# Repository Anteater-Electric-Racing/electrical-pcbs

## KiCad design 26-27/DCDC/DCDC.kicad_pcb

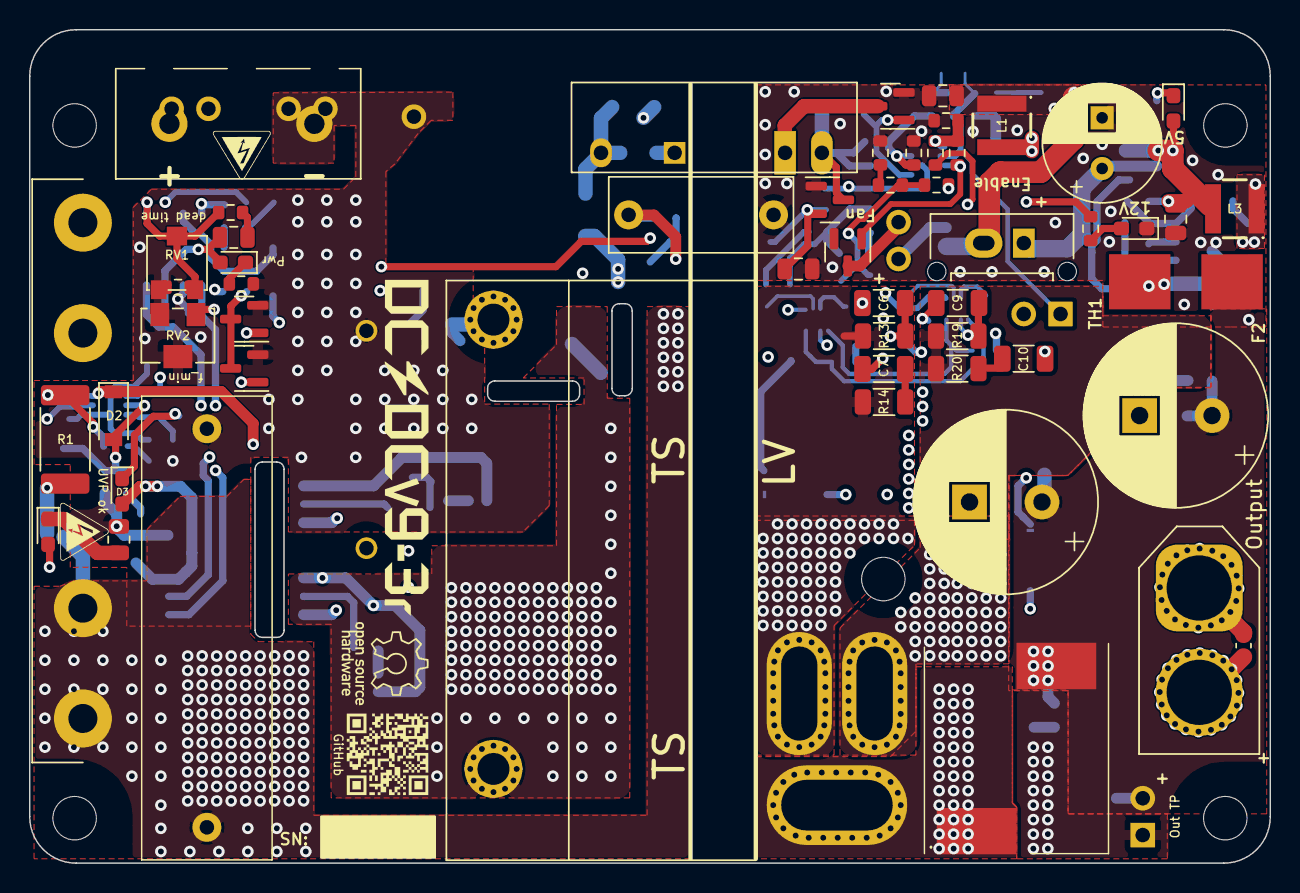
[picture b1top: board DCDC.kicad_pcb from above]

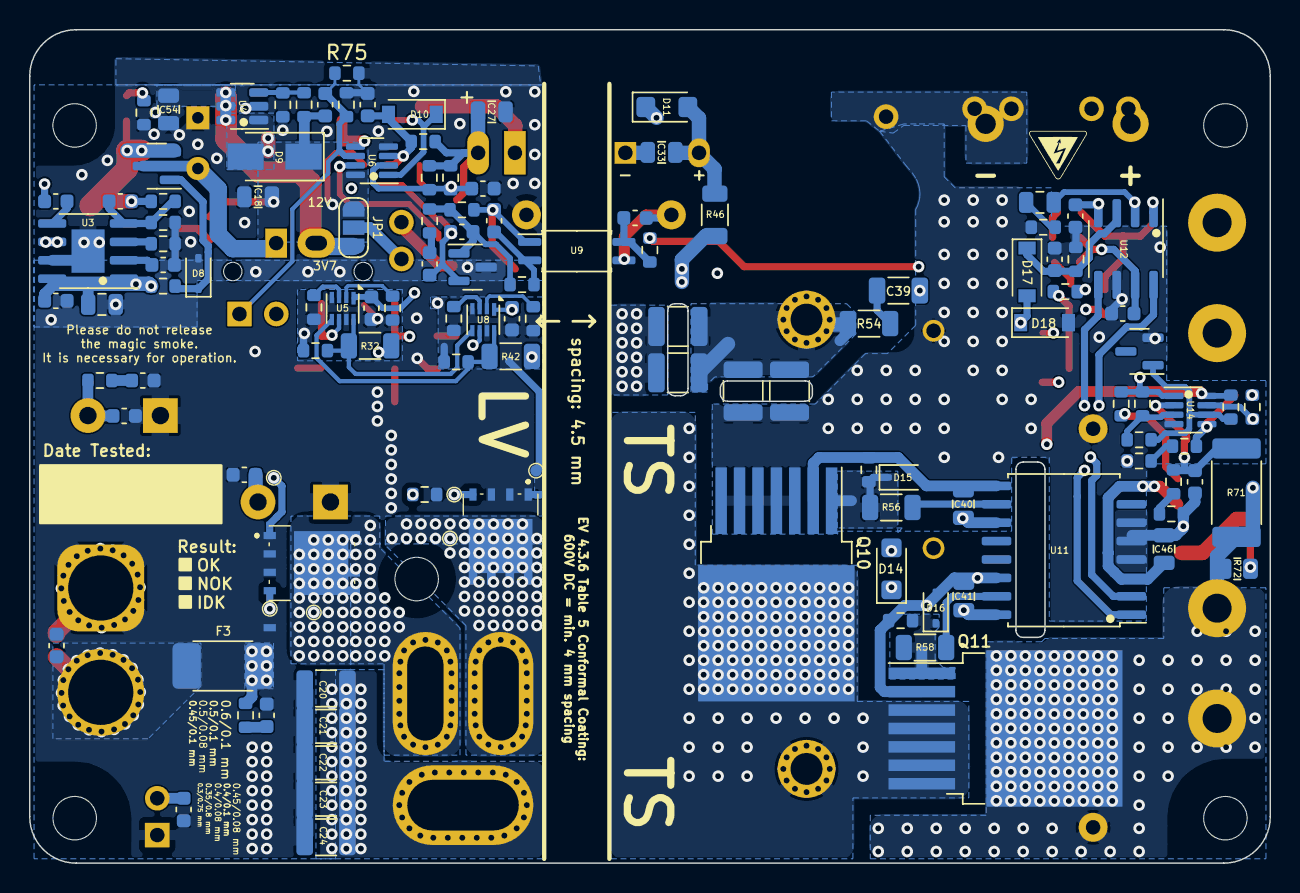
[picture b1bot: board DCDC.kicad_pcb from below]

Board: 4 copper layers, 85.6 x 57.5 mm, 189 parts (128 on the bottom side), 91 nets.

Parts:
C1: 2uF; MKP1848520704K2
C2, C15, C40, C41: 2.2uF; C_0805_2012Metric
C3: 22nF; R76UI22205050J
C4: 3.3nF; C_Disc_D12.5mm_W5.0mm_P10.00mm
C5, C33, C46: 10uF; C_0805_2012Metric
C6, C9: 1 nF; C_1206_3216Metric
C7, C10, C39: 470pF; C_1206_3216Metric
C8, C12, C18, C27, C42, C54: 22uF; C_0805_2012Metric
C11, C13: 2200uF; CP_Radial_D12.5mm_P5.00mm_symbol_inside
C14, C28: 100nF; C_0603_1608Metric
C16, C49, C50, C51, C52, C53, C55, C56, C57: 1nF; C_0603_1608Metric
C17, C19, C25, C31, C45: 1uF; C_0603_1608Metric
C20, C21, C22, C23, C24: 10uF; C_1210_3225Metric
C26, C44, C47: 22nF; C_0603_1608Metric
C29: 47pF; C_0603_1608Metric
C30, C32, C48: 10nF; C_0603_1608Metric
C34, C35, C36, C37: 5.6nF; C_1210_3225Metric
C43: 470nF; C_0603_1608Metric
C_start1: 3.8V 25F Supercap; CP_Radial_D8.0mm_P3.50mm
D1: HV_Orange; LED_0603_1608Metric_Pad1.05x0.95mm_HandSolder
D2, D10, D17, D18: 1N4448; D_SOD-123
D3, D4, D6, D7: Green; LED_0603_1608Metric_Pad1.05x0.95mm_HandSolder
D8, D15, D16: CDSOD323-T12; D_SOD-323
D9: SS1H10; D_SMA
D11, D14: VS-E7FX0212-M3/I; D_SMF
F1: 1.6A; Fuseholder0,25Zoll_32mm_littlefuse_102_122
F2: 500mA; NANO-0154-OMNI-BLOK-Fuse-Holder
F3: 20A; Bel_SMCF_Fuse_2410_6125Metric
HV_Logo_1, HV_Logo_1#2, HV_Logo_1#3: HV_Logo_1; HV_Logo_small
J1: Screw_Terminal_01x03; TerminalBlock_TE-282817-2_1x03_P5.00mm_90 Degrees updated v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
J2, J4, J6, J7, J8: Conn_01x02_Male; PinHeader_1x02_P2.54mm_Vertical
J3: Conn_01x02; Molex_Micro-Fit_3.0_43650-0215_1x02_P3.00mm_Vertical_combin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
J5: XT60 Male; AMASS_XT60-F_1x02_P7.20mm_Vertical
JP1: Fan Voltage Select; SolderJumper-3_P1.3mm_Open_RoundedPad1.0x1.5mm_NumberLabels
L1: 4.7uH; ASPI-4030S
L2: 1uH; 7443091100_v9.2
L3: 10uH; ASPI-4030S
NT1, NT2: NetTie_2; dummy_net_line_0.5mm
Q1, Q2, Q5, Q6, Q7: PMV20ENR; SOT-23
Q8, Q9: BSC027N06LS5ATMA1
Q10, Q11: IMBG65R050M2HXTMA1; TO-263-7_TabPin8
QR_Coode_1: QR_Coode; GitHub_QR_Code
R1, R71: 100M; R_2512_6332Metric_Pad1.40x3.35mm_HandSolder
R2, R72: 330k; R_0805_2012Metric
R3: 3.0k; R_0603_1608Metric
R4, R39, R41, R59, R61: 1k; R_0603_1608Metric
R5, R11, R15, R16, R21, R23, R30, R33, R40, R43, R55, R57, R63: 10k; R_0603_1608Metric
R10, R22, R29, R38: 2.2k; R_0603_1608Metric
R12: 910; R_0603_1608Metric
R13, R19: 100; R_1206_3216Metric
R14, R20: 47; R_1206_3216Metric
R17, R24: 27k; R_0603_1608Metric
R18, R27: 470k; R_0603_1608Metric
R25: 240k; R_0603_1608Metric
R26, R67, R70, R75: 100k; R_0603_1608Metric
R28, R34, R66: 33k; R_0603_1608Metric
R31, R36: 4.7k; R_0603_1608Metric
R32, R42: 4.7; R_1206_3216Metric
R35: 330k; R_0603_1608Metric
R37: 47k; R_0603_1608Metric
R44: 510; R_0603_1608Metric
R46: 20; R_1206_3216Metric
R54: 10M; R_1206_3216Metric
R56, R58: 10; R_1206_3216Metric
R60: 82k; R_0603_1608Metric
R62, R69: 100M; R_0603_1608Metric
R64: 820k; R_0603_1608Metric
R65: 510k; R_0603_1608Metric
R68: 1.6M; R_0603_1608Metric
R73, R74: 10; R_0603_1608Metric
RV1: 20k; Potentiometer_Bourns_PVG3G
RV2: 10k; Potentiometer_Bourns_3214W_Vertical
T1: DIY Transformer ETD 39; Transformer_ETD39_uprightV3.6 (PSS 24V)
TH2: 1k PTC; R_0603_1608Metric
TP1, TP2, TP3, TP4, TP5, TP6: TestPoint; TestPoint_Pad_D0.8mm_DC-DC
TP8: GaN GND2; TestPoint_Pad_D0.8mm_DC-DC
U1: TBA 1-1212HI; Converter_DCDC_TRACO_TBA 1-1212HI-3kV-iso
U2: RT9058-90GVL; SOT-23
U3: MP4541_SOP8-EP; SOIC-8-1EP_3.9x4.9mm_P1.27mm_EP2.29x3mm XL7005
U4: TLV61048DBVR; SOT-23-6
U5, U8: NCP4305DMTTWG; WDFN-8_2x2mm_P0.5mm
U6, U14: LM2904BIDDFR; SOT-23-8_DC-DC_v9
U7: TL431; SOT-23
U9: ACPL-217-50AE; SOIC-4_4.55x2.6mm_P1.27mm
U11: UCC21520DWR; SOIC-16W_7.5x10.3mm_P1.27mm
U12: UCC25600; SOIC-8_3.9x4.9mm_P1.27mm
U13: ZXRE330ASA-7; SOT-23

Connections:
24V_TP: C11.1, C13.1, C50.2, C51.2, C52.2, F2.1, F3.1, J4.1, L2.2, R17.1, R73.1, R74.1
+3V7: C8.1, C54.1, J3.2, JP1.3 (B), L1.1, U4.4 (~SHDN), U4.5 (IN), U4.6 (nc)
+9V: C5.1, C30.2, R39.1, U2.2 (VO), U9.1
+12V_HS: C41.2, D14.1 (K), U11.16 (VDDA)
+12V_IN: C2.2, C40.2, C45.2, C46.1, D2.1 (K), D3.2 (A), D4.2 (A), D11.1 (K), R70.1, U11.3 (VCCI), U11.8 (VCCI), U11.11 (VDDB), U12.7 (VCC), U14.8 (V+)
+12V_sw: C18.1, C19.2, C25.1, C27.1, C31.1, D9.1 (K), J8.1, JP1.1 (A), R16.1, R21.2, R27.1, R34.1, R35.2, R36.2, U1.1 (+VIN), U2.3 (VI), U5.1 (VCC), U6.8 (V+), U8.1 (VCC)
+24V: C15.2, C53.2, F2.2, R26.2, U3.1 (EN), U3.8 (VIN)
+HV: C1.2, C34.1, C35.1, F1.2, Q11.8 (D), R1.1, R71.1, R72.1
+HV_in: F1.1, J1.2, J7.1, J7.2
-HV_in: C1.1, C3.2, C4.1, C32.2, C33.2, C36.2, C37.2, C43.2, C44.1, C45.1, C46.2, C47.2, D18.2 (A), J1.1, J6.1, J6.2, Q1.2 (S), Q2.2 (S), Q10.3 (S), Q10.4 (S), Q10.5 (S), Q10.6 (S), Q10.7 (S), R2.2, R3.2, R5.1, R59.2, R60.1, R65.2, R68.2, RV1.3, RV2.2, RV2.3, U1.5 (-VOUT), U9.3, U11.4 (GND), U11.5 (DIS), U11.6 (DT), U12.6 (GND), U13.2, U14.4 (V-)
/HB_out: Q10.8 (D), Q11.3 (S), Q11.4 (S), Q11.5 (S), Q11.6 (S), Q11.7 (S), T1.1 (AA)
/HS: U11.1 (INA), U12.8 (GD1)
/LS: U11.2 (INB), U12.5 (GD2)
/OC: C44.2, D17.1 (K), R60.2, U12.3 (OC)
/OTP_FAN: Q5.1 (G), R18.1, U6.7
/OTP_OFF: D10.1 (K), Q6.1 (G), U6.1
/OVP: Q2.1 (G), R69.1, U14.7
/Opc+: C32.1, R44.2, U9.4
/Synchronous Rectification/3: Q9.5 (D_1), Q9.6 (D_2), Q9.7 (D_3), Q9.8 (D_4), Q9.9 (D_5), R13.2, R14.1, T1.3 (SB), TP5.1
/Synchronous Rectification/5: Q8.5 (D_1), Q8.6 (D_2), Q8.7 (D_3), Q8.8 (D_4), Q8.9 (D_5), R19.2, R20.1, T1.5 (SA), TP3.1
/UVP: Q1.1 (G), R62.1, R63.1, U14.1
GND: C4.2, C5.2, C7.1, C8.2, C10.1, C11.2, C12.1, C13.2, C15.1, C17.1, C18.2, C20.2, C21.2, C22.2, C23.2, C24.2, C27.2, C28.1, C48.1, C49.1, C50.1, C51.1, C52.1, C53.1, C54.2, C55.1, C56.1, C57.1, C_start1.2 (-), D6.1 (K), D8.2 (A2), J4.2, J5.2, NT1.2, NT2.2, Q5.2 (S), Q6.2 (S), Q8.1 (S_1), Q8.2 (S_2), Q8.3 (S_3), Q9.1 (S_1), Q9.2 (S_2), Q9.3 (S_3), R10.2, R11.2, R15.1, R22.1, R23.2, R25.1, R28.2, R31.1, R75.2, TH2.2, TP8.1, U2.1 (GND), U3.7 (GND), U4.2 (GND), U6.4 (V-), U7.3 (A)
unnamed: C2.1, R4.2
unnamed: C7.2, R14.2
unnamed: C10.2, R20.2
unnamed: C26.2, R37.1
unnamed: C30.1, R41.1, U9.2
unnamed: C39.2, R54.1
unnamed: C42.2, R59.1
unnamed: C56.2, R73.2
unnamed: C57.2, R74.2
unnamed: C_start1.1 (+), J3.1, Q7.3 (D)
unnamed: D1.2 (A), R72.2
unnamed: D1.1 (K), R2.1
unnamed: C47.1, D2.2 (A), R67.2, R71.2, U14.2 (-)
unnamed: D3.1 (K), R63.2
unnamed: D4.1 (K), R5.2
unnamed: D6.2 (A), R21.1
unnamed: C12.2, C16.2, D7.2 (A), L3.2, Q7.2 (S), R24.1
unnamed: D7.1 (K), R22.2
unnamed: D8.1 (A1), Q7.1 (G), R26.1
unnamed: D9.2 (A), L1.2, U4.1 (SW)
unnamed: C48.2, D10.2 (A), R11.1, R34.2, U6.3 (+)
unnamed: C33.1, D11.2 (A), R46.2, U1.7 (+VOUT)
unnamed: D14.2 (A), R46.1
unnamed: D15.1 (A1), Q10.1 (G), R55.1, R56.1
unnamed: C40.1, D15.2 (A2), Q10.2 (DS), R55.2, U11.9 (VSSB)
unnamed: D16.1 (A1), Q11.1 (G), R57.1, R58.1
unnamed: C41.1, D16.2 (A2), Q11.2 (DS), R57.2, U11.14 (VSSA)
unnamed: C39.1, D17.2 (A), D18.1 (K)
unnamed: J2.1, JP1.2 (C)
unnamed: J2.2, Q5.3 (D)
unnamed: C49.2, C55.2, F3.2, J5.1
unnamed: C19.1, J8.2, R31.2, R75.1, U6.6 (-)
unnamed: Q1.3 (D), Q2.3 (D), R61.1
unnamed: Q8.4 (G), R32.1, TP2.1
unnamed: Q9.4 (G), R42.1, TP4.1
unnamed: R10.1, R12.2
unnamed: R65.1, R66.2
unnamed: R67.1, R68.1
unnamed: C34.2, C35.2, C36.1, C37.1, R54.2, T1.2 (AB)
unnamed: C20.1, C21.1, C22.1, C23.1, C24.1, L2.1, T1.4 (SC)
unnamed: C14.2, U3.5 (BST)
unnamed: C16.1, R23.1, R24.2, U3.4 (FB)
unnamed: R25.2, U3.3 (FREQU)
unnamed: C14.1, L3.1, U3.6 (SW)
unnamed: C17.2, U3.2 (VCC)
unnamed: R27.2, R28.1, U4.3 (FB)
unnamed: C9.2, R19.1, U5.6 (CS)
unnamed: R30.2, R32.2, U5.8 (DRV), U8.5 (TRIG/DIS)
unnamed: C9.1, C25.2, NT1.1, R29.1, R30.1, R33.1, TP1.1, U5.4 (LLD), U5.7 (GND)
unnamed: R33.2, U5.2 (MIN_TOFF)
unnamed: R29.2, U5.3 (MIN_TON)
unnamed: R40.2, R42.2, U5.5 (TRIG/DIS), U8.8 (DRV)
unnamed: C28.2, R35.1, R36.1, TH2.1, U6.2 (-)
unnamed: R15.2, R16.2, R18.2, U6.5 (+)
unnamed: C29.2, R37.2, R39.2, R41.2, U7.1 (K)
unnamed: C26.1, C29.1, R12.1, R17.2, U7.2 (REF)
unnamed: C6.2, R13.1, U8.6 (CS)
unnamed: C6.1, C31.2, NT2.1, R38.1, R40.1, R43.1, TP6.1, U8.4 (LLD), U8.7 (GND)
unnamed: R43.2, U8.2 (MIN_TOFF)
unnamed: R38.2, U8.3 (MIN_TON)
unnamed: R58.2, U11.15 (OUTA)
unnamed: R56.2, U11.10 (OUTB)
unnamed: R3.1, R4.1, RV1.1, RV1.2, U12.1 (DT)
unnamed: C42.1, R44.1, RV2.1, U12.2 (RT)
unnamed: C43.1, R61.2, U12.4 (SS)
unnamed: R62.2, R64.1, U14.3 (+)
unnamed: R1.2, R66.1, R69.2, U14.5 (+)
unnamed: R64.2, R70.2, U13.1, U14.6 (-)
OTP_FET: Q6.3 (D), U1.2 (-VIN)

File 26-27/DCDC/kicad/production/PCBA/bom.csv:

Designator,Footprint,Quantity,Value,LCSC Part #
C1,MKP1848520704K2,1,2uF,
"C11, C13",CP_Radial_D12.5mm_P5.00mm_symbol_inside,2,2200uF,
"C12, C18, C27, C42, C54, C8",0805,6,22uF,
"C14, C28",0603,2,100nF,
"C15, C40, C41",0805,3,2.2uF,
"C16, C49, C50, C51, C52, C53, C56, C57",0603,8,1nF,
"C17, C19, C25, C31, C45",0603,5,1uF,
"C20, C21, C22, C23, C24",1210,5,10uF,
"C26, C44, C47",0603,3,22nF,
C29,0603,1,47pF,
"C30, C32, C48",0603,3,10nF,
"C33, C46, C5",0805,3,10uF,
"C34, C35, C36, C37",1210,4,5.6nF,
C39,1206,1,470pF,
C4,C_Disc_D12.5mm_W5.0mm_P10.00mm,1,3.3nF,
C43,0603,1,470nF,
"C6, C9",1206,2,1 nF,
C_START1,CP_Radial_D8.0mm_P3.50mm,1,3.8V 25F Supercap,
D1,0603,1,HV_Orange,
"D10, D17, D18, D2",D_SOD-123,4,1N4448,
"D11, D12, D14",D_SMF,3,VS-E7FX0212-M3/I,
"D13, D9",D_SMA,2,SS1H10,
"D15, D16, D8",D_SOD-323,3,CDSOD323-T12,
"D3, D4, D5, D6, D7",0603,5,Green,
F1,"Fuseholder0,25Zoll_32mm_littlefuse_102_122",1,1.6A,
F2,NANO-0154-OMNI-BLOK-Fuse-Holder,1,500mA,
F3,Bel_SMCF_Fuse_2410_6125Metric,1,20A,
J1,43650-03YY_151617,1,43650-0315,
"J2, J4, J8",PinHeader_1x02_P2.54mm_Vertical,3,Conn_01x02_Male,
J3,Molex_Micro-Fit_3.0_43650-0215_1x02_P3.00mm_Vertical_combined2.54pinheader,1,Conn_01x02,
J5,AMASS_XT60-F_1x02_P7.20mm_Vertical,1,XT60 Male,
JP1,SolderJumper-3_P1.3mm_Open_RoundedPad1.0x1.5mm_NumberLabels,1,Fan Voltage Select,
L1,ASPI-4030S,1,4.7uH,
L2,7443091100_v9.2,1,1uH,
L3,ASPI-4030S,1,10uH,
"Q1, Q2, Q5, Q6, Q7",SOT-23,5,PMV20ENR,
"Q10, Q11",TO-263-7_TabPin8,2,IMBG65R050M2HXTMA1,
Q3,TO-220-3_Vertical_HV1.2mm,1,SIHP24N80AE-GE3,
Q4,TO-220-3_Vertical_HV1.2mm,1,IXYP8N90C3,
"Q8, Q9",BSC027N06LS5ATMA1,2,BSC027N06LS5ATMA1,
"R1, R71",2512,2,100M,
"R10, R22, R29, R38, R48, R49, R8",0603,7,2.2k,
"R11, R15, R16, R21, R23, R30, R33, R40, R43, R5, R51, R52, R55, R57, R63, R7, R9",0603,17,10k,
R12,0603,1,910,
"R13, R19",1206,2,100,
"R17, R24",0603,2,27k,
"R18, R27, R50",0603,3,470k,
"R2, R72",0805,2,330k,
R25,0603,1,240k,
"R26, R45, R47, R53, R67, R70, R75",0603,7,100k,
"R28, R34, R66",0603,3,33k,
"R31, R36",0603,2,4.7k,
"R32, R42",1206,2,4.7,
R35,0603,1,330k,
R37,0603,1,47k,
"R39, R41, R59, R61",0603,4,1k,
R44,0603,1,510,
R46,1206,1,20,
R54,1206,1,10M,
"R56, R58",1206,2,10,
R6,1206,1,47,
R60,0603,1,82k,
"R62, R69",0603,2,100M,
R64,0603,1,820k,
R65,0603,1,510k,
R68,0603,1,1.6M,
"R73, R74",0603,2,10,
RV1,Potentiometer_Bourns_PVG3G,1,20k,
RV2,Potentiometer_Bourns_3214W_Vertical,1,10k,
T1,Transformer_ETD39_uprightV3.6 (PSS 24V),1,DIY Transformer ETD 39,
TH2,0603,1,1k PTC,
U1,Converter_DCDC_TRACO_TBA 1-1212HI-3kV-iso,1,RP-1212S,
"U10, U14, U6",SOT-23-8_DC-DC_v9,3,LM2904BIDDFR,
U11,SOIC-16W_7.5x10.3mm_P1.27mm,1,UCC21520DW,
U12,SOIC-8_3.9x4.9mm_P1.27mm,1,UCC25600,
U13,SOT-23,1,ZXRE330ASA-7,
U2,SOT-23,1,RT9058-90GVL,
U3,SOIC-8-1EP_3.9x4.9mm_P1.27mm_EP2.29x3mm XL7005,1,MP4541_SOP8-EP,
U4,SOT-23-6,1,TLV61048DBVR,
"U5, U8",WDFN-8_2x2mm_P0.5mm,2,NCP4305DMTTWG,
U7,SOT-23,1,TL431BCDBZR,
U9,SOIC-4_4.55x2.6mm_P1.27mm,1,ACPL-217-50AE,

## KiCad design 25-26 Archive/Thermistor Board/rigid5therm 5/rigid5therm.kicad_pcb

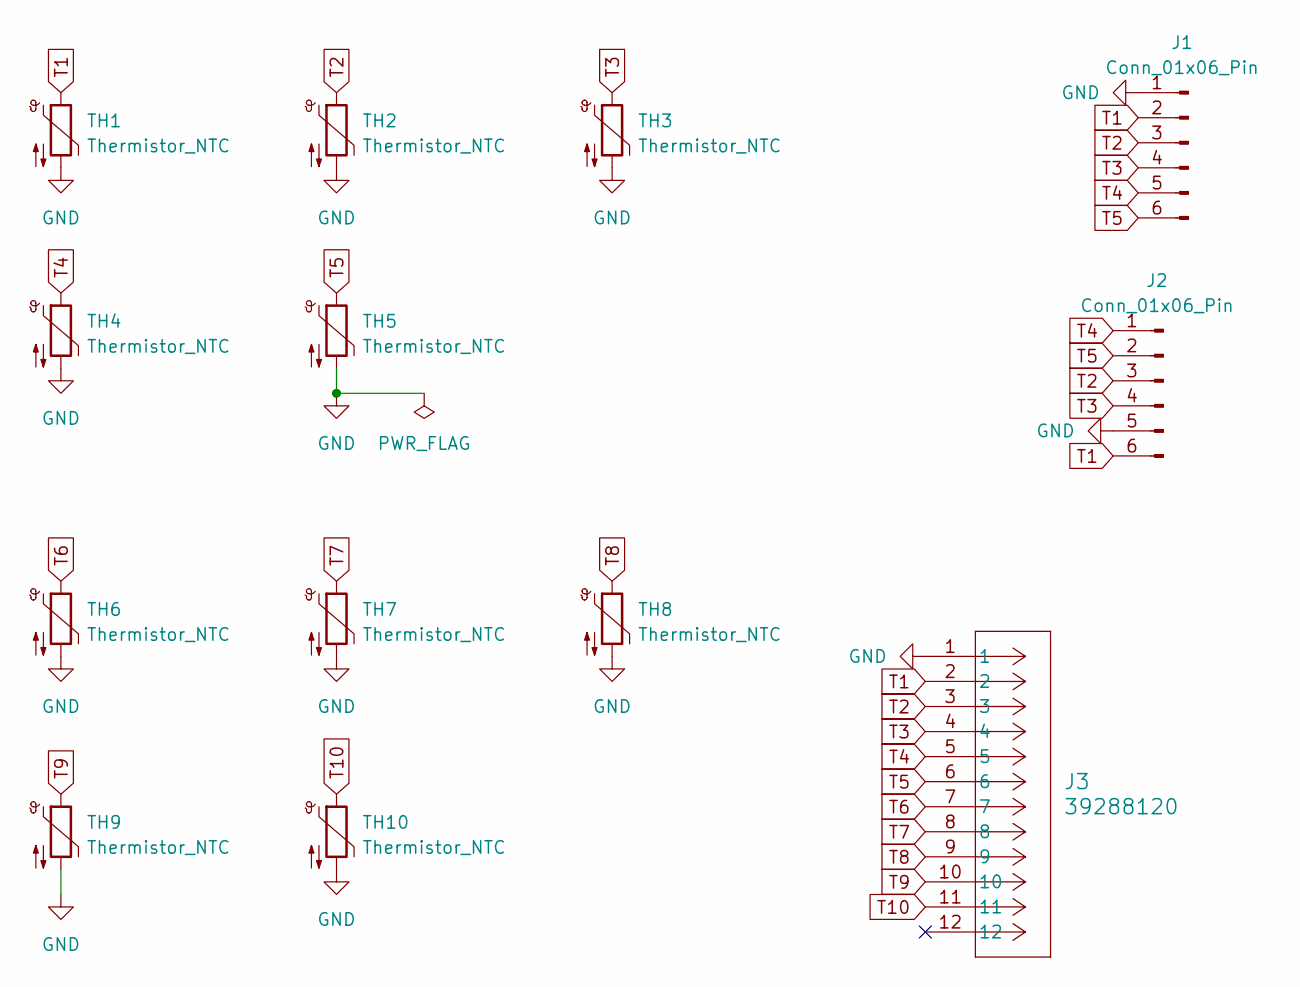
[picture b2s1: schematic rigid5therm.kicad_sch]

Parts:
J1, J2: Conn_01x06_Pin; PinHeader_2x03_P2.54mm_Vertical
J3: 39288120; CONN_SD-5566-002_12_MOL
TH1, TH2, TH3, TH4, TH5, TH6, TH7, TH8, TH9, TH10: Thermistor_NTC; Thermistor_NTCLE413

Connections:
GND: J1.1, J2.5, J3.1, TH1.2, TH2.2, TH3.2, TH4.2, TH5.2, TH6.2, TH7.2, TH8.2, TH9.2, TH10.2
T1: J1.2, J2.6, J3.2, TH1.1
T2: J1.3, J2.3, J3.3, TH2.1
T3: J1.4, J2.4, J3.4, TH3.1
T4: J1.5, J2.1, J3.5, TH4.1
T5: J1.6, J2.2, J3.6, TH5.1
T6: J3.7, TH6.1
T7: J3.8, TH7.1
T8: J3.9, TH8.1
T9: J3.10, TH9.1
T10: J3.11, TH10.1

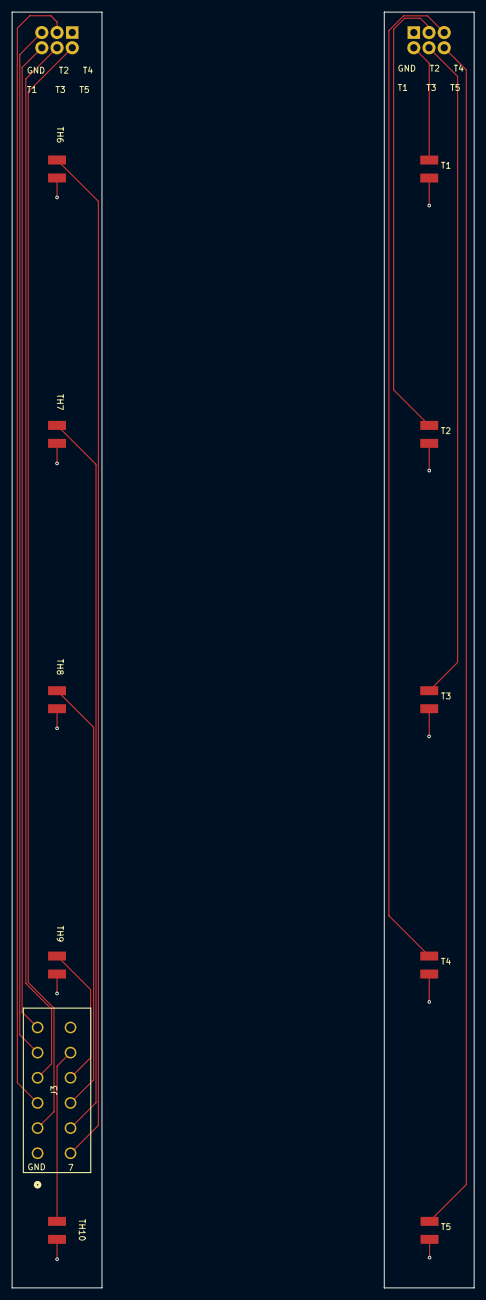
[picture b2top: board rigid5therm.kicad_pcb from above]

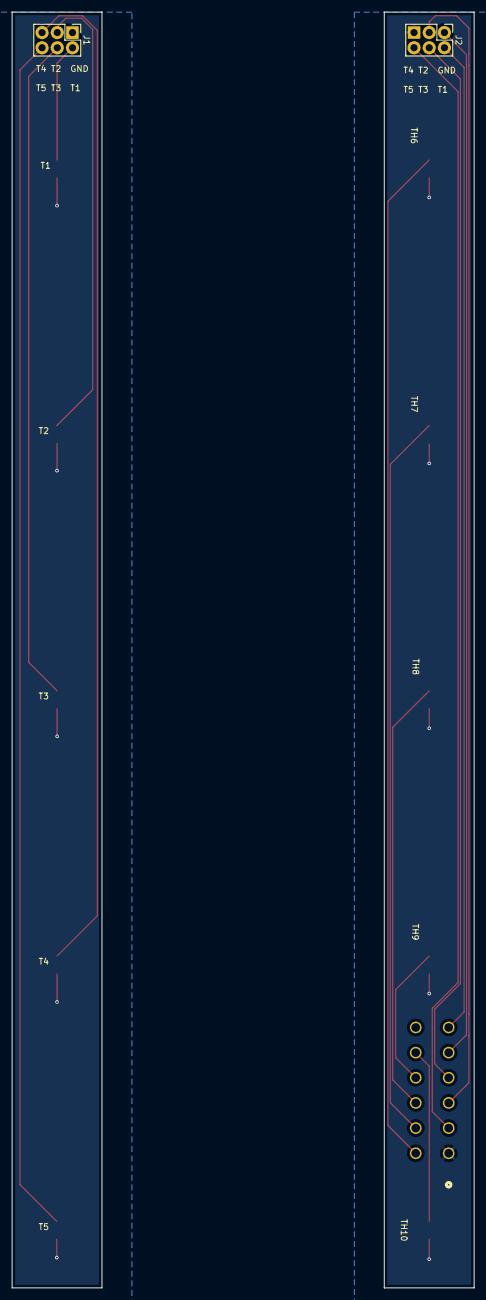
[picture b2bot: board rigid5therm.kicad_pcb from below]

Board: 2 copper layers, 77.1 x 213.0 mm, 13 parts (2 on the bottom side), 11 nets.

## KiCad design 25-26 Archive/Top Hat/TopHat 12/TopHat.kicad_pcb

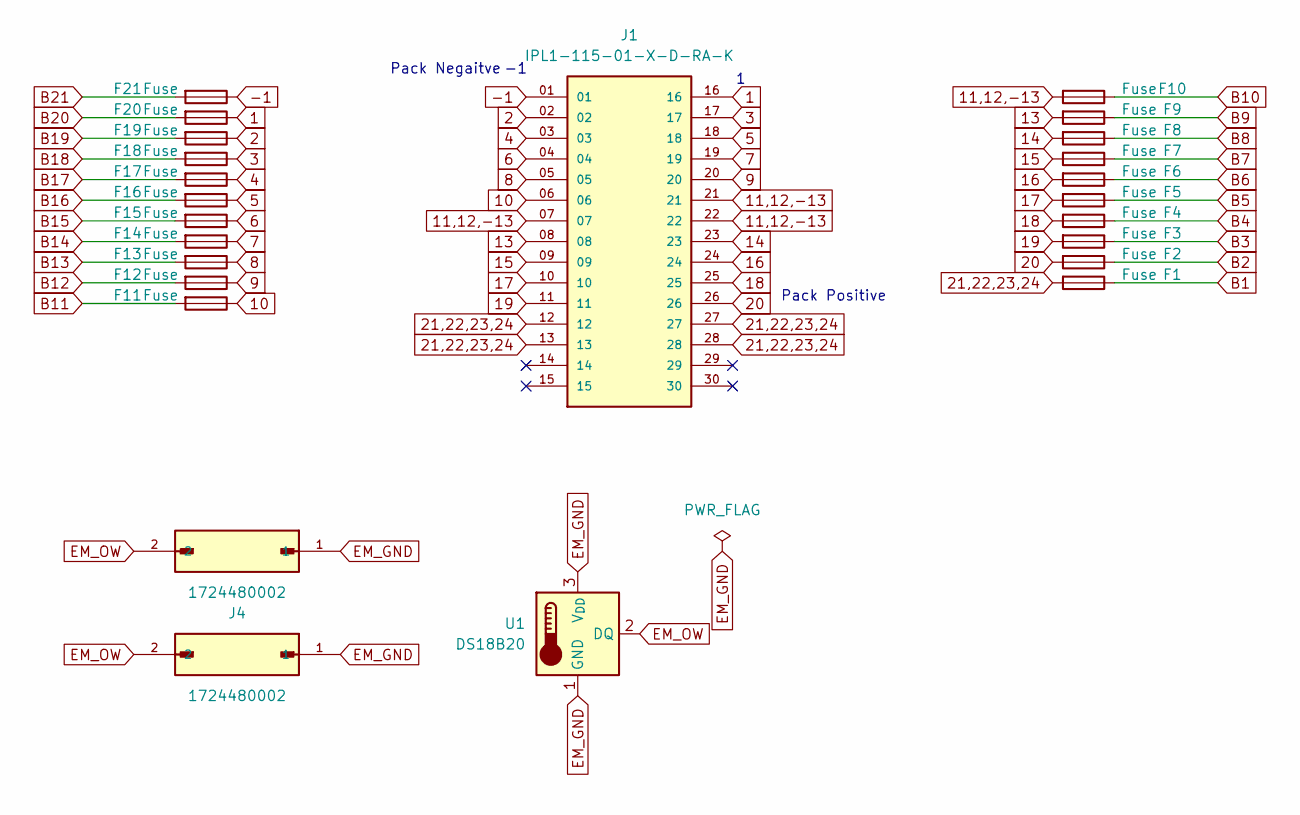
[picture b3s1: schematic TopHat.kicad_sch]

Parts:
F1, F2, F3, F4, F5, F6, F7, F8, F9, F10, F11, F12, F13, F14, F15, F16, F17, F18, F19, F20, F21: Fuse; FUSC6125X279N; MANUFACTURER PART NUMBER 0679L0500-01
J1: IPL1-115-01-X-D-RA-K; SAMTEC_IPL1-115-01-X-D-RA-K; PARTREV E
J2, J4: 1724480002; MOLEX_1724480002; PARTREV A
U1: DS18B20; TO-92_Inline; MANUFACTURER PART NUMBER Analog Devices Inc./Maxim Integrated

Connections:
1: F20.1, J1.16
2: F19.1, J1.02
3: F18.1, J1.17
4: F17.1, J1.03
5: F16.1, J1.18
6: F15.1, J1.04
7: F14.1, J1.19
8: F13.1, J1.05
9: F12.1, J1.20
10: F11.1, J1.06
11,12,-13: F10.2, J1.07, J1.21, J1.22
13: F9.2, J1.08
14: F8.2, J1.23
15: F7.2, J1.09
16: F6.2, J1.24
17: F5.2, J1.10
18: F4.2, J1.25
19: F3.2, J1.11
20: F2.2, J1.26
21,22,23,24: F1.2, J1.12, J1.13, J1.27, J1.28
-1: F21.1, J1.01
B1: F1.1
B2: F2.1
B3: F3.1
B4: F4.1
B5: F5.1
B6: F6.1
B7: F7.1
B8: F8.1
B9: F9.1
B10: F10.1
B11: F11.2
B12: F12.2
B13: F13.2
B14: F14.2
B15: F15.2
B16: F16.2
B17: F17.2
B18: F18.2
B19: F19.2
B20: F20.2
B21: F21.2
EM_GND: J2.1, J4.1, U1.1 (GND), U1.3 (V_{DD})
EM_OW: J2.2, J4.2, U1.2 (DQ)

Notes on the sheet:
Pack Negaitve
Pack Positive

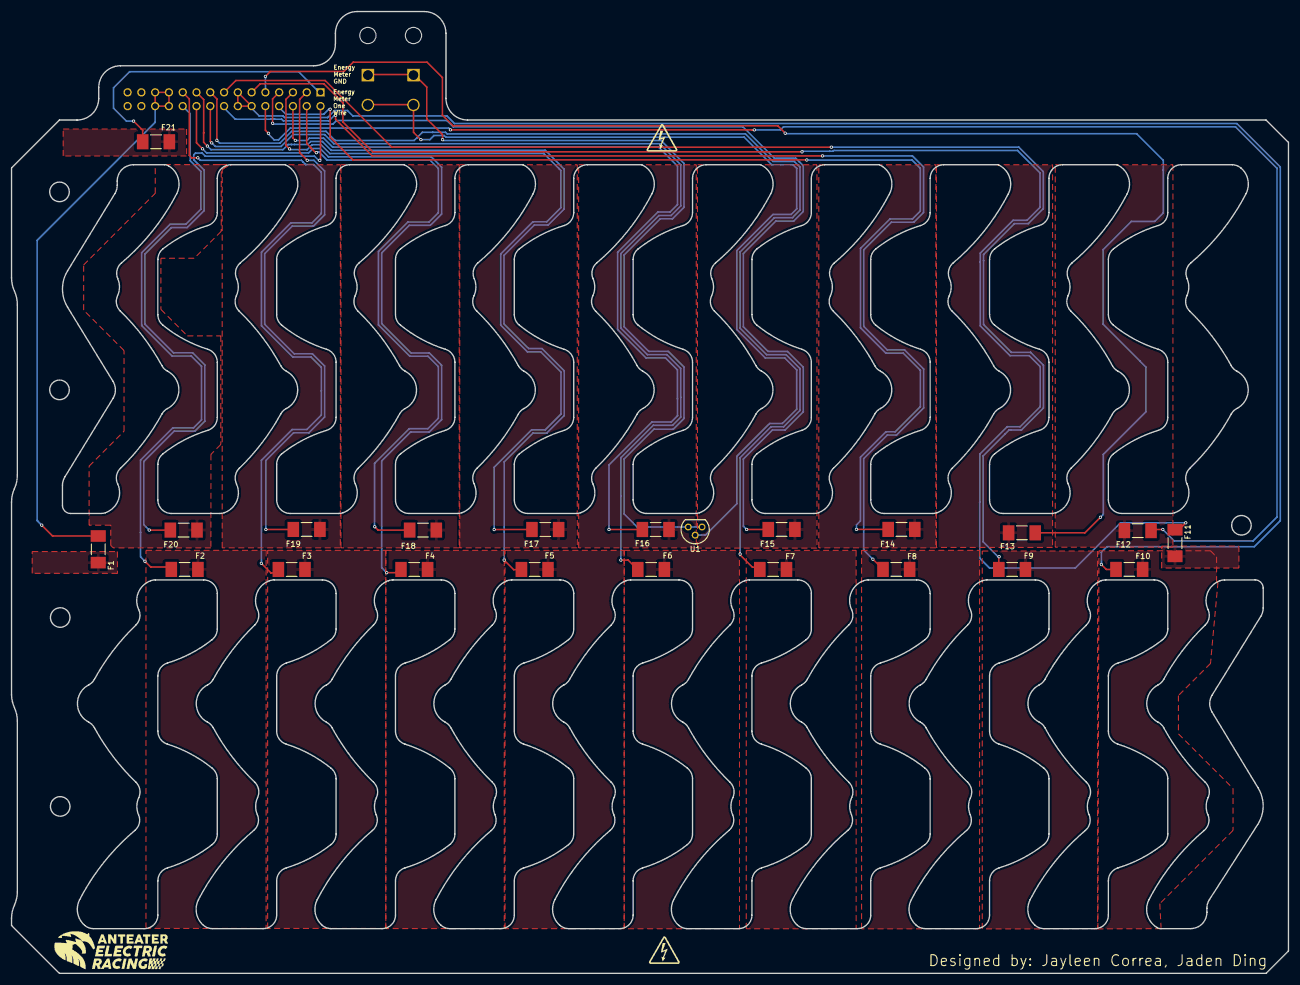
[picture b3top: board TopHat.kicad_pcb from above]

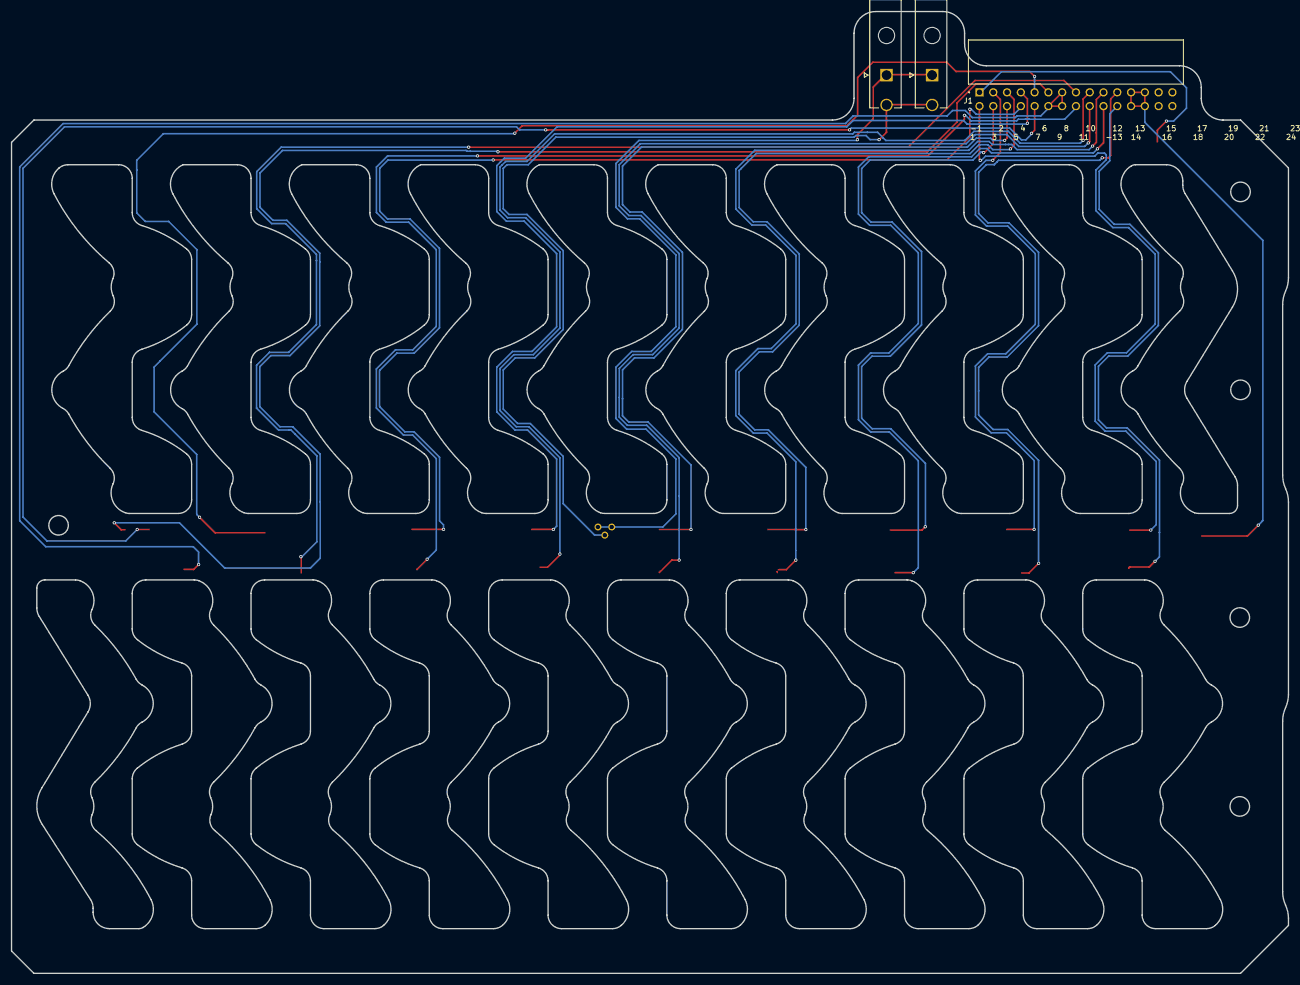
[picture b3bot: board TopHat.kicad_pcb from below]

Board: 2 copper layers, 235.4 x 177.3 mm, 25 parts (3 on the bottom side), 23 nets.

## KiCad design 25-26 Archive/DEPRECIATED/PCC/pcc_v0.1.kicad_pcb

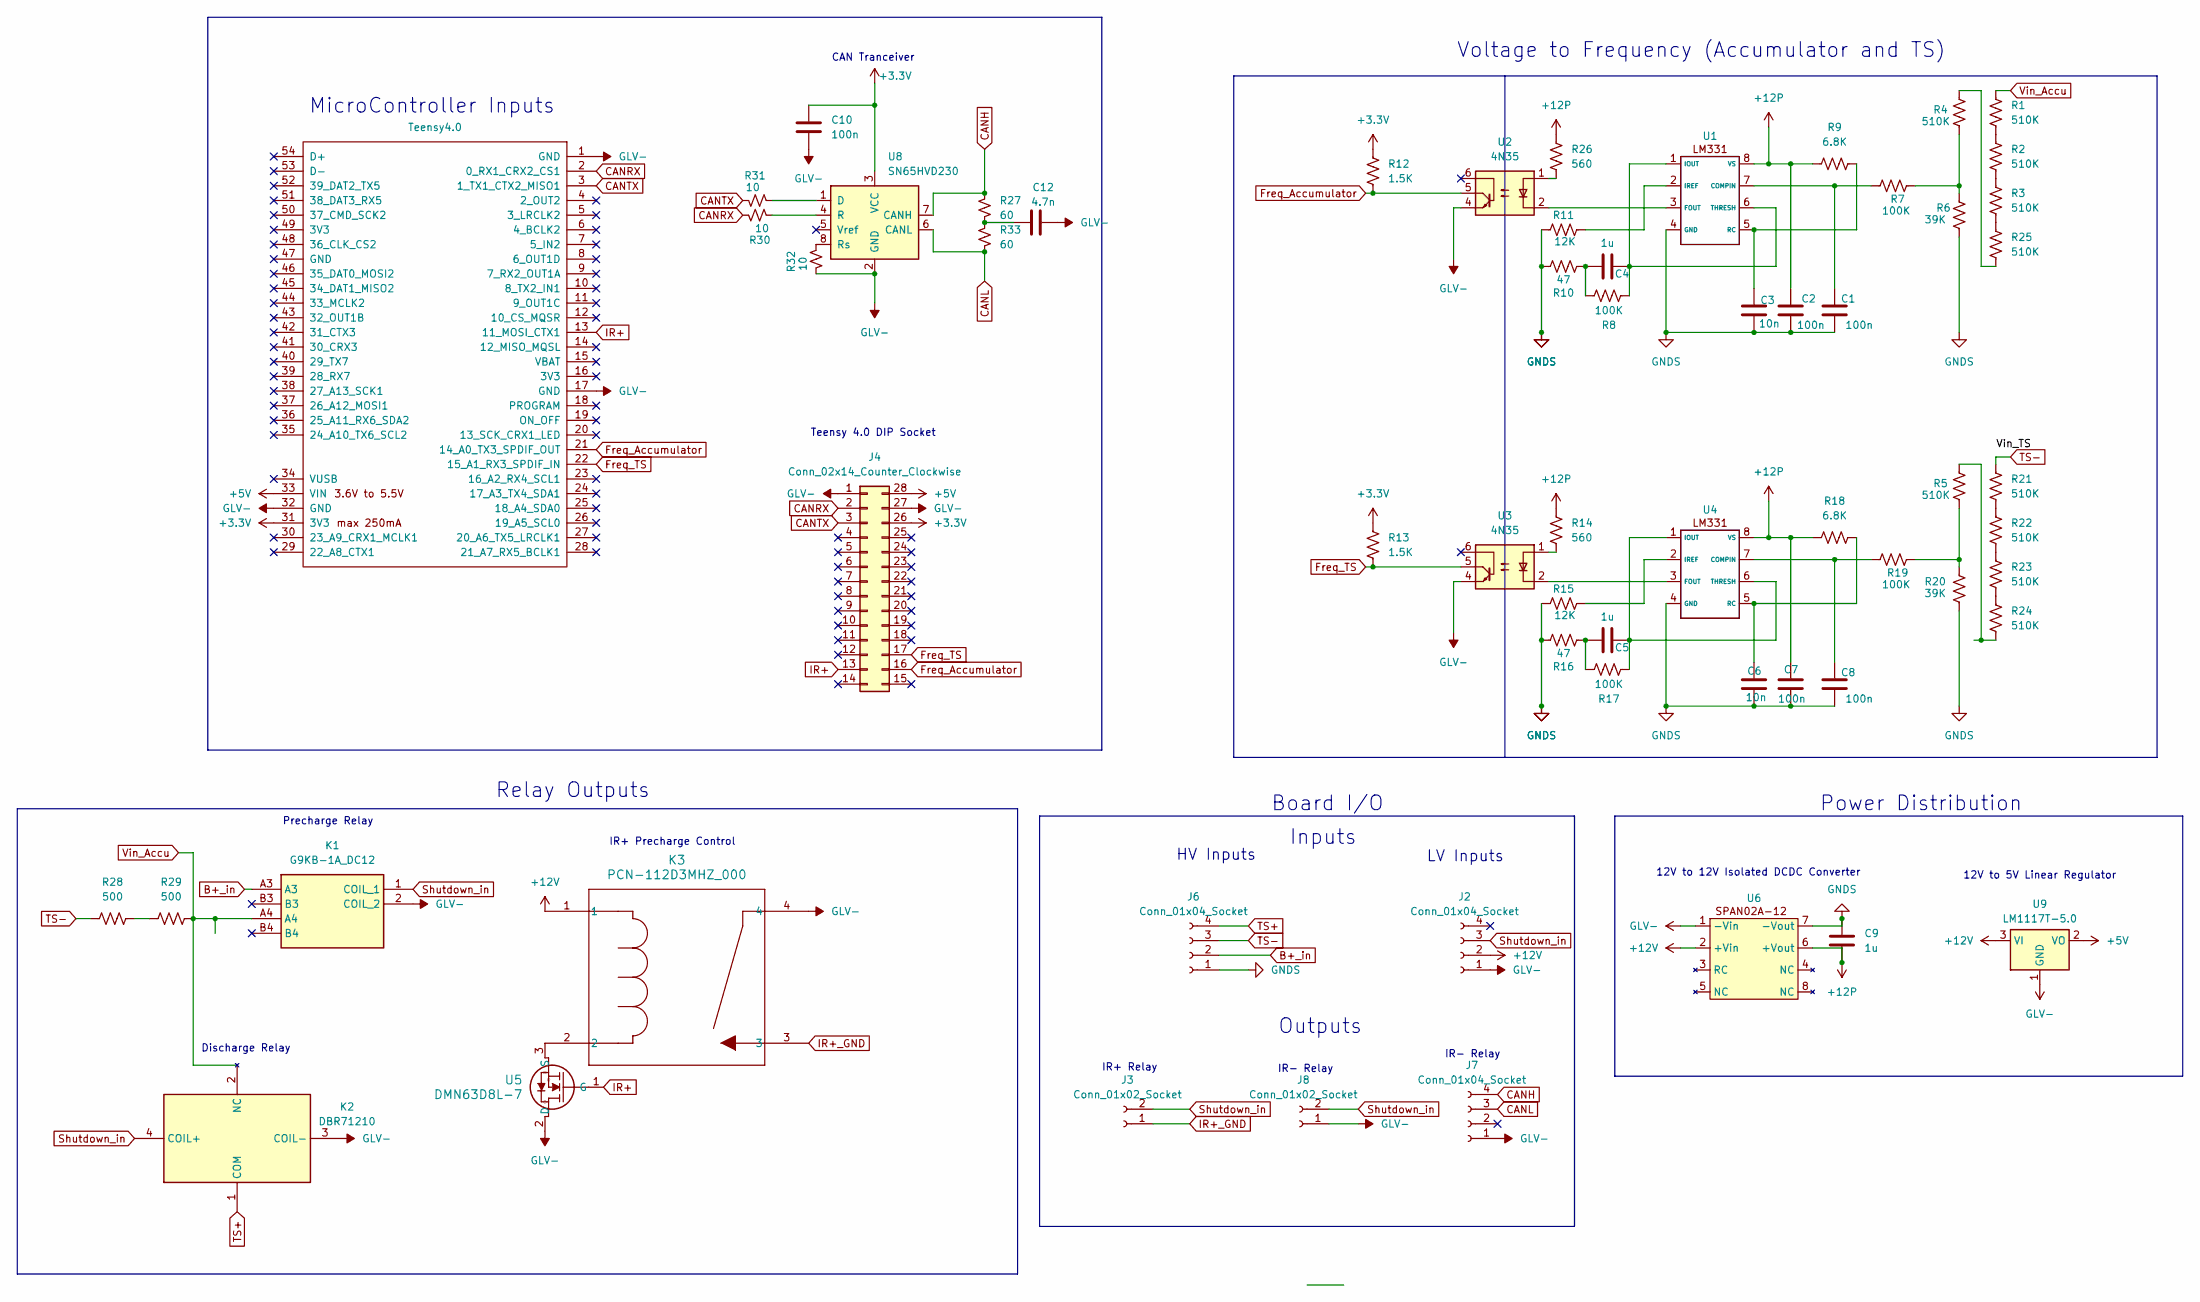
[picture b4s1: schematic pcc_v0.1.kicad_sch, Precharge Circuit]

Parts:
C1, C2, C7, C8, C10: 100n; C_0805_2012Metric
C3, C6: 10n; C_0805_2012Metric
C4, C5, C9: 1u; C_0805_2012Metric
C12: 4.7n; C_0805_2012Metric
J2, J6, J7: Conn_01x04_Socket; Molex_Mini-Fit_Jr_5566-04A2_2x02_P4.20mm_Vertical
J3, J8: Conn_01x02_Socket; Molex_Mini-Fit_Jr_5566-02A2_2x01_P4.20mm_Vertical
J4: Conn_02x14_Counter_Clockwise; DIP-28_W15.24mm_Socket
K1: G9KB-1A_DC12; G9KB1ADC12; Mouser Part Number 653-G9KB-1ADC12
K2: DBR71210; Mouser Part Number 285-DBR71210
K3: PCN-112D3MHZ_000; RELAY_PCN-105D3MHZ_000_TEC
R1, R2, R3, R4, R5, R21, R22, R23, R24, R25: 510K; R_0805_2012Metric
R6, R20: 39K; R_0805_2012Metric
R7, R8, R17, R19: 100K; R_0805_2012Metric
R9, R18: 6.8K; R_0805_2012Metric
R10, R16: 47; R_0805_2012Metric
R11, R15: 12K; R_0805_2012Metric
R12, R13: 1.5K; R_0805_2012Metric
R14, R26: 560; R_0805_2012Metric
R27, R33: 60; R_0805_2012Metric
R28, R29: 500; Ohmite HS100 500R F
R30, R31, R32: 10; R_0805_2012Metric
U1, U4: DIP-8_W7.62mm_Socket
U2, U3: 4N35; DIP-6_W7.62mm_Socket
U5: DMN63D8L-7; SOIC_63D8L-7_DIO
U6: SIP-8_19x3mm_P2.54mm
U7: Teensy4.0; DIP-28_W15.24mm_Socket
U8: SN65HVD230; SOIC-8_3.9x4.9mm_P1.27mm
U9: LM1117T-5.0; TO-220-3_Horizontal_TabDown

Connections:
+3.3V: C10.1, J4.26, R12.2, R13.2, U7.31 (3V3), U8.3 (VCC)
+5V: J4.28, U7.33 (VIN), U9.2 (VO)
+12P: C2.1, C7.1, C9.2, R9.1, R14.1, R18.1, R26.1, U1.8 (VS), U4.8 (VS), U6.6 (+Vout)
+12V: J2.2, K3.1, U6.2 (+Vin), U9.3 (VI)
B+_in: J6.2, K1.A3
CANH: J7.4, R27.1, U8.7 (CANH)
CANL: J7.3, R33.2, U8.6 (CANL)
CANRX: J4.2, R30.1, U7.2 (0_RX1_CRX2_CS1)
CANTX: J4.3, R31.2, U7.3 (1_TX1_CTX2_MISO1)
Freq_Accumulator: J4.16, R12.1, U2.5, U7.21 (14_A0_TX3_SPDIF_OUT)
Freq_TS: J4.17, R13.1, U3.5, U7.22 (15_A1_RX3_SPDIF_IN)
GLV-: C10.2, C12.2, J2.1, J4.1, J4.27, J7.1, J8.1, K1.2 (COIL_2), K2.3 (COIL-), K3.4, R32.2, U2.4, U3.4, U5.2 (D), U6.1 (-Vin), U7.1 (GND), U7.17 (GND), U7.32 (GND), U8.2 (GND), U9.1 (GND)
GNDS: C1.2, C2.2, C3.2, C6.2, C7.2, C8.2, C9.1, J6.1, R6.2, R10.2, R11.1, R15.1, R16.2, R20.2, U1.4 (GND), U4.4 (GND), U6.7 (-Vout)
IR+: J4.13, U5.1 (G), U7.13 (11_MOSI_CTX1)
IR+_GND: J3.1, K3.3
unnamed: C4.1, R8.1, R10.1
unnamed: C5.1, R16.1, R17.1
unnamed: C12.1, R27.2, R33.1
unnamed: R1.2, R2.1
unnamed: R2.2, R3.1
unnamed: R4.2, R6.1, R7.2
unnamed: R14.2, U3.1
unnamed: R5.2, R19.2, R20.1
unnamed: R21.2, R22.1
unnamed: R22.2, R23.1
unnamed: R23.2, R24.1
unnamed: R5.1, R24.2
unnamed: R3.2, R25.1
unnamed: R4.1, R25.2
unnamed: R26.2, U2.1
unnamed: R28.2, R29.1
unnamed: C1.1, R7.1, U1.7 (COMPIN)
unnamed: U1.3 (FOUT), U2.2
unnamed: C4.2, R8.2, U1.1 (IOUT), U1.6 (THRESH)
unnamed: R11.2, U1.2 (IREF)
unnamed: C3.1, R9.2, U1.5 (RC)
unnamed: C8.1, R19.1, U4.7 (COMPIN)
unnamed: U3.2, U4.3 (FOUT)
unnamed: C5.2, R17.2, U4.1 (IOUT), U4.6 (THRESH)
unnamed: R15.2, U4.2 (IREF)
unnamed: C6.1, R18.2, U4.5 (RC)
unnamed: K3.2, U5.3 (S)
unnamed: R31.1, U8.1 (D)
unnamed: R30.2, U8.4 (R)
unnamed: R32.1, U8.8 (Rs)
Shutdown_in: J2.3, J3.2, J8.2, K1.1 (COIL_1), K2.4 (COIL+)
TS+: J6.4, K2.1 (COM)
TS-: J6.3, R21.1, R28.1
Vin_Accu: K1.A4, K2.2 (NC), R1.1, R29.2

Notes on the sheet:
Board I/O
HV Inputs
Inputs
IR+ Relay
LV Inputs
Teensy 4.0 DIP Socket
Voltage to Frequency (Accumulator and TS)
MicroController Inputs
IR- Relay
Relay Outputs
Discharge Relay
CAN Tranceiver
Precharge Relay
IR+ Precharge Control
Outputs
Power Distribution
12V to 5V Linear Regulator
12V to 12V Isolated DCDC Converter

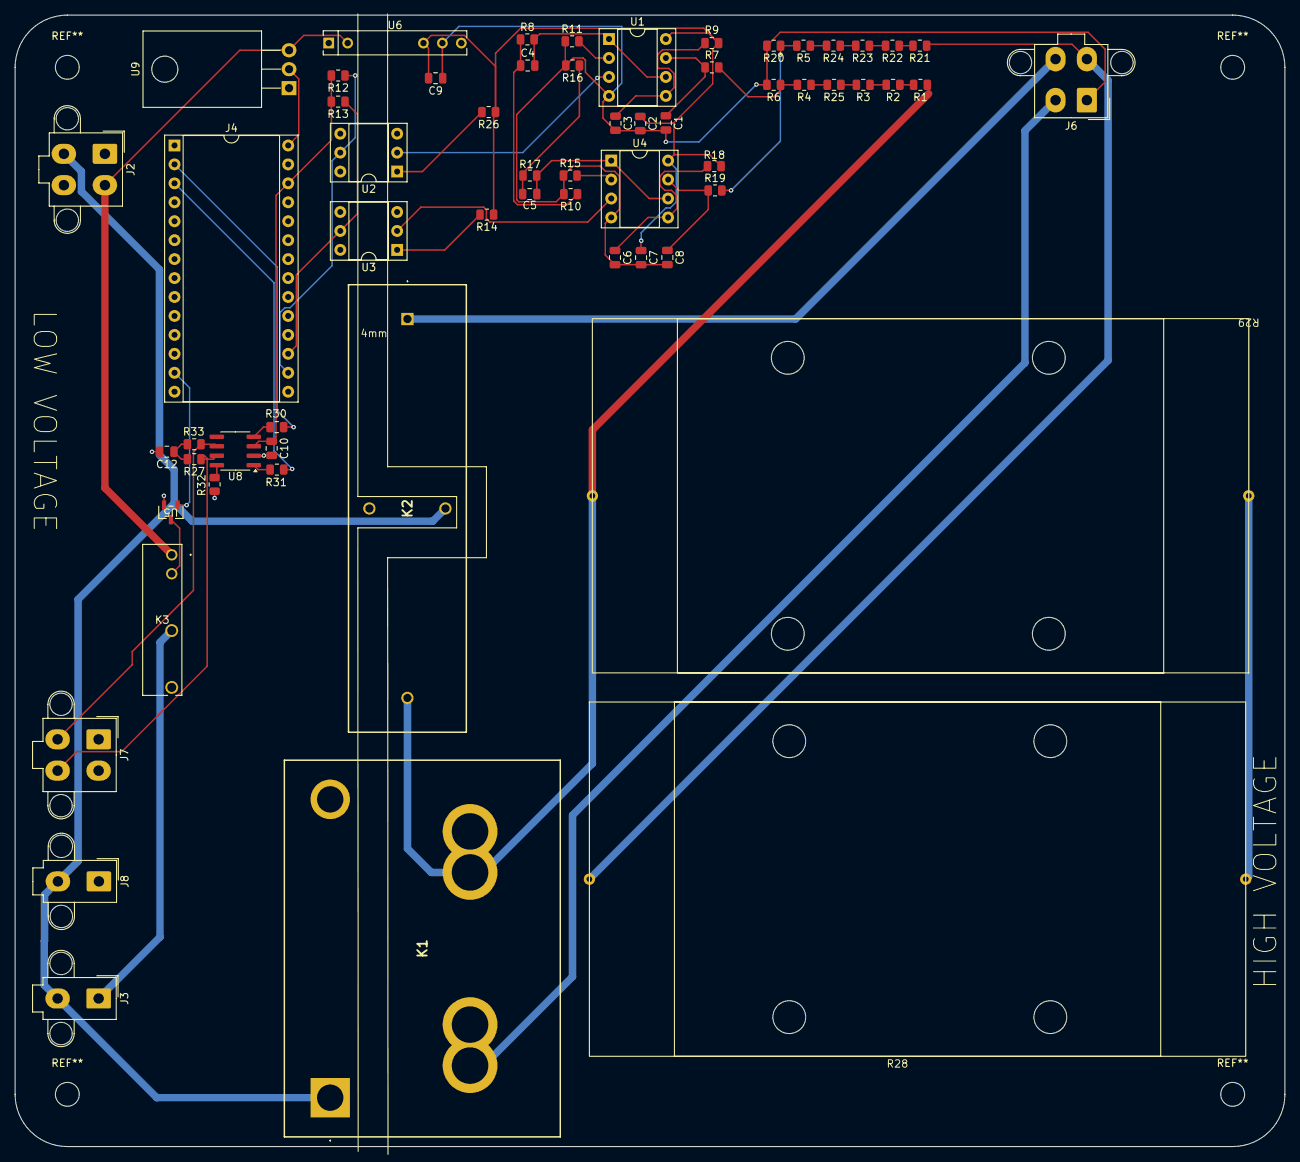
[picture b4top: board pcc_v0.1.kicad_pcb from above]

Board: 2 copper layers, 170.3 x 151.7 mm, 61 parts (0 on the bottom side), 49 nets.
